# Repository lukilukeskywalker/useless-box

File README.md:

# useless-box
Code and kicad files for the useless box i have designed. http://www.thingiverse.com/thing:2210764

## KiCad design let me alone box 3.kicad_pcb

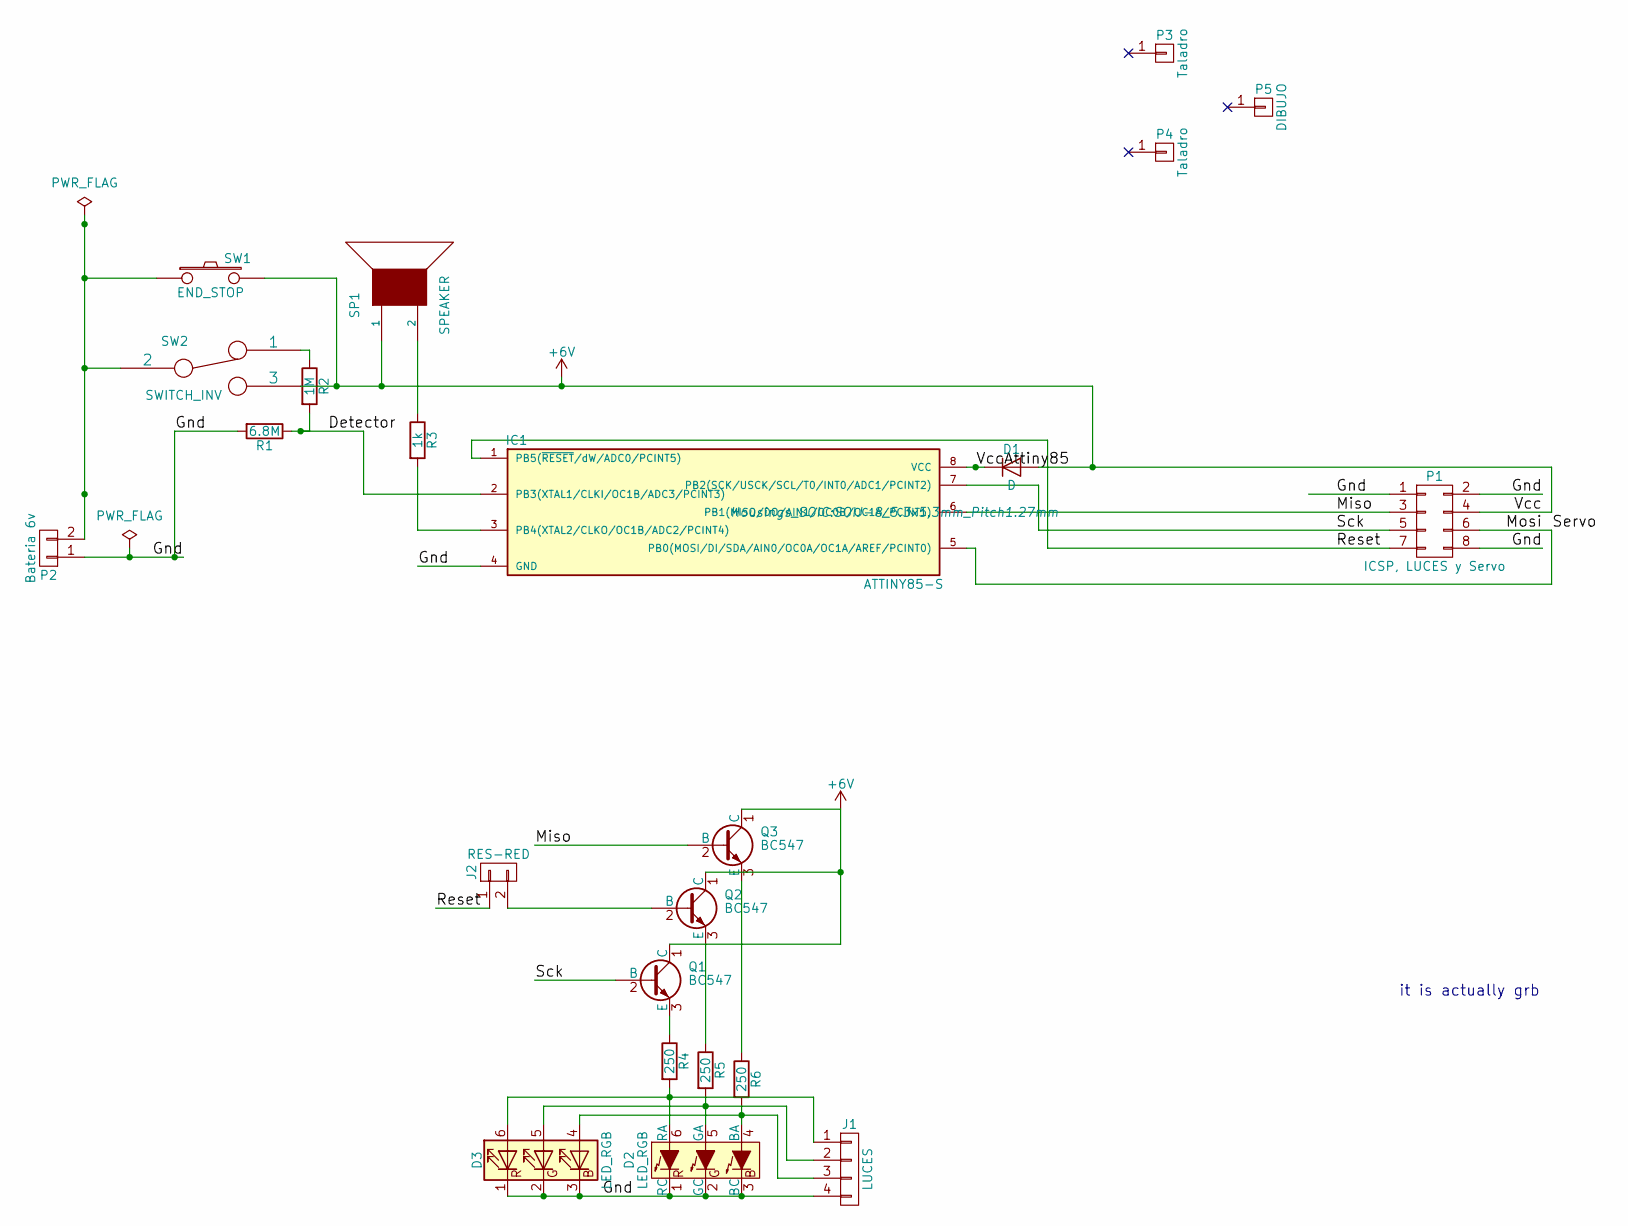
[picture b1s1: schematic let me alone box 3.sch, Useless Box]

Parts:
D1: D; Diode_DO-35_SOD27_Horizontal_RM10
D2, D3: LED_RGB; LED_WS2812-PLCC6
IC1: ATTINY85-S; SOIJ-8_5.3x5.3mm_Pitch1.27mm
J1: LUCES; Socket_Strip_Straight_1x04_Pitch2.54mm
J2: RES-RED; Pin_Header_Straight_1x02_Pitch2.54mm
P1: ICSP, LUCES y Servo; Socket_Strip_Straight_2x04
P2: Bateria 6v; Socket_Strip_Straight_1x02
P3, P4: Taladro; MountingHole_2.7mm
P5: DIBUJO; KiCad-Logo_6mm_SilkScreen
Q1, Q2, Q3: BC547; TO-92_Molded_Narrow
R1: 6.8M; R_Axial_DIN0207_L6.3mm_D2.5mm_P10.16mm_Horizontal
R2: 1M; R_Axial_DIN0207_L6.3mm_D2.5mm_P10.16mm_Horizontal
R3: 1k; R_Axial_DIN0207_L6.3mm_D2.5mm_P10.16mm_Horizontal
R4, R5, R6: 250; R_Axial_DIN0204_L3.6mm_D1.6mm_P7.62mm_Horizontal
SP1: SPEAKER; Buzzer_12x9.5RM7.6
SW1: END_STOP; Socket_Strip_Straight_1x02_Pitch2.54mm
SW2: SWITCH_INV; SW_NKK_G1xJP

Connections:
+6V: D1.2 (A), P1.4, Q1.1 (C), Q2.1 (C), Q3.1 (C), SP1.1, SW1.2, SW2.3
/Detector: IC1.2 (PB3(XTAL1/CLKI/OC1B/ADC3/PCINT3)), R1.1, R2.2
/Gnd: D2.1 (RC), D2.2 (GC), D2.3 (BC), D3.1 (RK), D3.2 (GK), D3.3 (BK), IC1.4 (GND), J1.4, P1.1, P1.2, P1.8, P2.1, R1.2
/Miso: IC1.6 (PB1(MISO/DO/AIN1/OC0B/OC1A/PCINT1)), P1.3, Q3.2 (B)
/Mosi: IC1.5 (PB0(MOSI/DI/SDA/AIN0/OC0A/OC1A/AREF/PCI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), P1.6
/Reset: IC1.1 (PB5(~RESET~/dW/ADC0/PCINT5)), J2.1, P1.7
/Sck: IC1.7 (PB2(SCK/USCK/SCL/T0/INT0/ADC1/PCINT2)), P1.5, Q1.2 (B)
/VccAttiny85: D1.1 (K), IC1.8 (VCC)
unnamed: D2.4 (BA), D3.4 (BA), J1.3, R6.2
unnamed: D2.5 (GA), D3.5 (GA), J1.2, R5.2
unnamed: D2.6 (RA), D3.6 (RA), J1.1, R4.2
unnamed: IC1.3 (PB4(XTAL2/CLKO/OC1B/ADC2/PCINT4)), R3.2
unnamed: J2.2, Q2.2 (B)
unnamed: P2.2, SW1.1, SW2.2
unnamed: Q1.3 (E), R4.1
unnamed: Q2.3 (E), R5.1
unnamed: Q3.3 (E), R6.1
unnamed: R2.1, SW2.1
unnamed: R3.1, SP1.2

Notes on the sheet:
it is actually grb

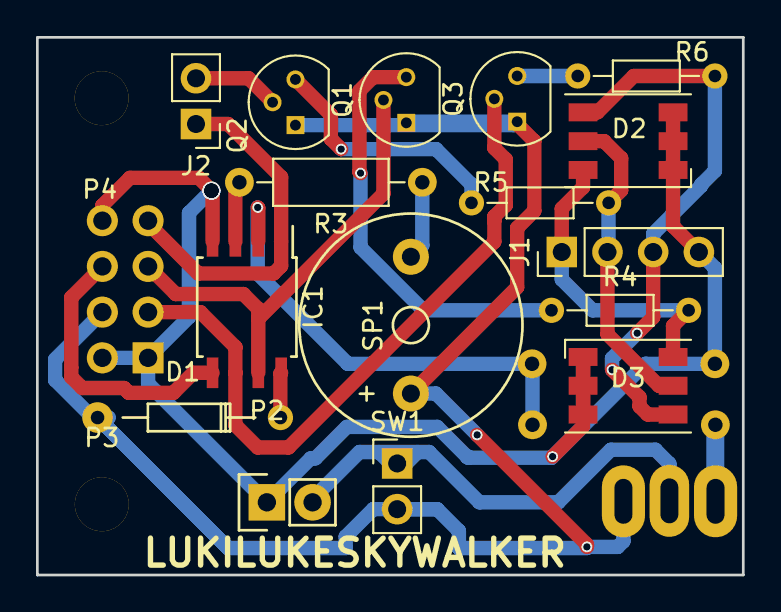
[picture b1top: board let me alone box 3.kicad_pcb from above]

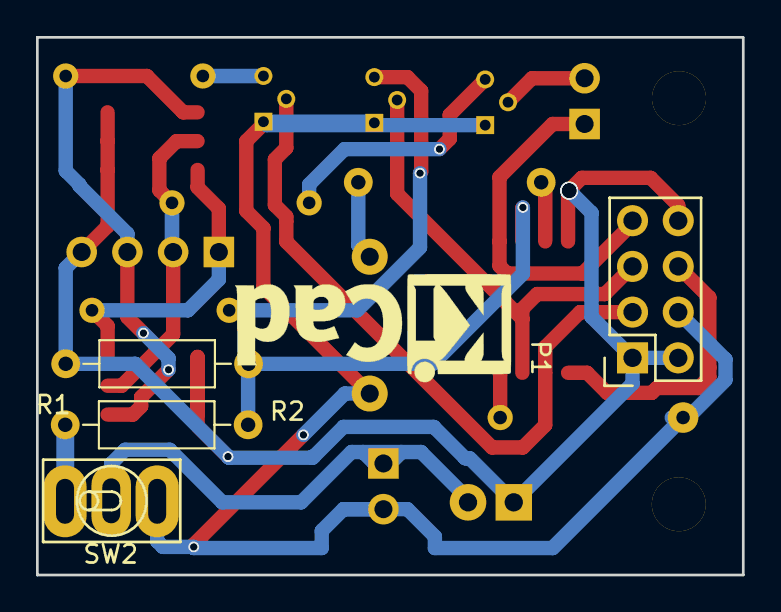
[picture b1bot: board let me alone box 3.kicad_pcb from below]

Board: 2 copper layers, 39.2 x 29.9 mm, 23 parts (5 on the bottom side), 19 nets.

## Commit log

2017-04-04 Add files via upload
    Kicad files for the pcb. This should be the last version. Version 4 is actually Version 3, and viceversa... but hey... now it is version 3 final aproach
2017-04-04 Add files via upload
    Arduino sketch and hex code for attiny85... i must tell u the fuses for this to work. It works but it is still not finished. i want to add more variables, solve the buzzer problem and make it to swic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
